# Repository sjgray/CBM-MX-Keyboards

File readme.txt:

CBM MX Keyboards Project         Steve J. Gray
========================

This is a project to create replacement keyboards for CBM Machines
using standard MX keyswitches. The first goal is to create direct
replacements that fit standard CBM cases (if possible).

KEYBOARDS
=========

Keyboards are identified by a string in the following format:

KB-Vn-Rn

where: KB is the keyboard name
       Vn is the version#. This is a unique design/layout of a specific keyboard.
       Rn is the revision#. Generally updates to a specific keyboard version.

 So, take the PET "B" keyboard. V1-R1 is the first design using pcb cutouts to allow the
keyboard to be mounted higher. When this was awkward a R2 revision was done to eliminate
the cutouts and reduce the pcb size. However this requires a 3D printed bracket to mount
it. Since both keyboards use the same switch and keycap layout both are V1. If a new
version is designed that say uses a different sized spacebar or has significant changes
then a V2 would be made. With the CLCD keyboard there are two versions. V1 has a layout
using the diamond arrow cursor keys. A V2 version instead uses an inverted-T cursor layout.

Examples:

       "B-V1-R1" is the PET/CBM "B" (Business) keyboard, Version 1, Revision 1
       "N-V1-R2" is the PET/CBM "N" (Normal/Graphic) keyboard, Version1 , Revision 2

Keyboards In Development:

	N    = PET/CBM Normal/Graphic Keyboard (4032)
	B    = PET/CBM Business Keyboard (8032, SuperPET, 8296 etc)
	CBM2 = B128, CBM128-80, 5x0, 6x0, 7x0,P500 etc
	V364 = TED series prototype with numeric pad
	CLCD = Laptop prototype
	CSX  = C128+SX64 customizable design

Planned:
	C64  = VIC-20, C64, C16 etc
	C65  = C65 with cursor keys etc
	B64  = PET "B" with C64-style layout

STICKERS
========

 Artwork for labelling keycaps is in the STICKERS folder, since that is the most likely
way to label the keys. However, stickers is not the only possibility... see webpage for
more details.

SCANS
=====

  Original keycap scans are in the SCANS folder. These are scanned with a flatbed scanner,
either the entire keyboard (stitched if required) or individual keycap top and front.

WEBPAGE
=======

For more information please visit the project webpage.
Comments and feedback are welcome!

http://www.cbmsteve.ca/mxkeyboards/index.html

HISTORY
=======

KEYBOARD    DATE        PCB?	STATUS
--------    ----        ----	------
B-V1-R1     2020-07-01  YES	Built and tested. Electrically working but requires pcb mounting hole modifications
N-V1-R1     2020-12-17  YES	Built and tested. Electrically working but does not fit in N keyboard case due to measurement error.
N/B         2021-02-10  -	Add keyboard labelling stickers for both N and B keyboards on one page.
N-V1-R2     2021-03-31  -	Add Gerbers
B-V1-R2     2023-03-21	YES	Released. Built and tested.
CSX-V1-R1   2023-09-01  YES	Testing...
CSX-V1-R1   2024-02-25  YES     Released. Built 3 configurations. Basic functionality is working but more work is needed to fully test.
V364        2024-02-25  YES     Released. Built and tested.

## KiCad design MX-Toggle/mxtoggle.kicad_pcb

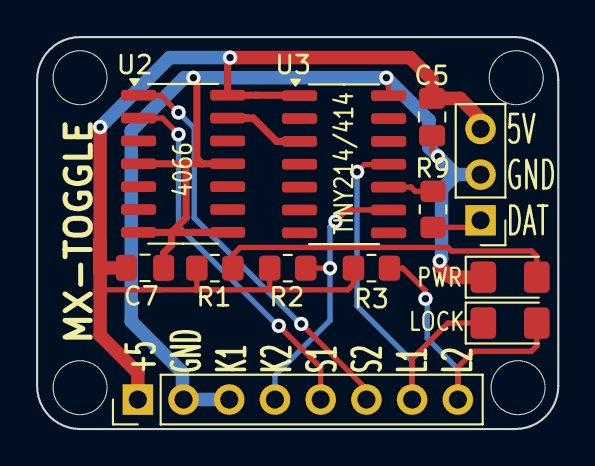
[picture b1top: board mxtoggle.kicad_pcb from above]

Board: 2 copper layers, 29.0 x 21.8 mm, 12 parts (0 on the bottom side), 11 nets.

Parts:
C5, C7: 0.1uf; C_0805_2012Metric_Pad1.18x1.45mm_HandSolder
D1: POWER; D_1206_3216Metric_Pad1.42x1.75mm_HandSolder
D3: SL-LED; D_1206_3216Metric_Pad1.42x1.75mm_HandSolder
J1: HEADER; PinHeader_1x08_P2.54mm_Vertical
J7: UPDI; PinHeader_1x03_P2.54mm_Vertical
R1: 330; R_0805_2012Metric_Pad1.20x1.40mm_HandSolder
R2, R3: R; R_0805_2012Metric_Pad1.20x1.40mm_HandSolder
R9: 470 ohm; R_0805_2012Metric_Pad1.20x1.40mm_HandSolder
U2: CD4066BM; SO-14_3.9x8.65mm_P1.27mm
U3: ATtiny214-SS; SOIC-14_3.9x8.7mm_P1.27mm

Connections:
5V: C5.1, C7.1, J1.1, J7.3, R1.1, R2.1, R3.1, U2.14 (V_{DD}), U3.1 (VCC)
GND: C5.2, C7.2, D1.1 (K), J1.2, J1.3, J7.2, U2.4, U2.7 (V_{SS}), U2.8, U2.11, U3.14 (GND)
KEY: J1.4, R2.2, U3.9 (PB0)
LED1: D3.1 (K), J1.7, U3.11 (PA1)
LED2: D3.2 (A), J1.8, R3.2
unnamed: D1.2 (A), R1.2
unnamed: J7.1, R9.2
SLOUT: U2.13, U3.3 (PA5)
STATE1: J1.5, U2.2
STATE2: J1.6, U2.1
UPDI: R9.1, U3.10 (~RESET/PA0)

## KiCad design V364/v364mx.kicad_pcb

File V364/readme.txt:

V364 MX Keyboard
================

This is a keyboard for the never-released V364 computer which was part of the TED series.
I designed this keyboard based on pictures of prototype machines as part of my project
to recreate the computer. The project is still in development.

I am releasing the design for people that might want a V364 keyboard for their PLUS/4 or
C16 computer which could be placed in a 3D-printed case.

The keyboard is tested and works. The numeric pad does not require any special software
to work as the keys are wired up as duplicates of existing keys in the regular PLUS/4
keyboard.

Steve

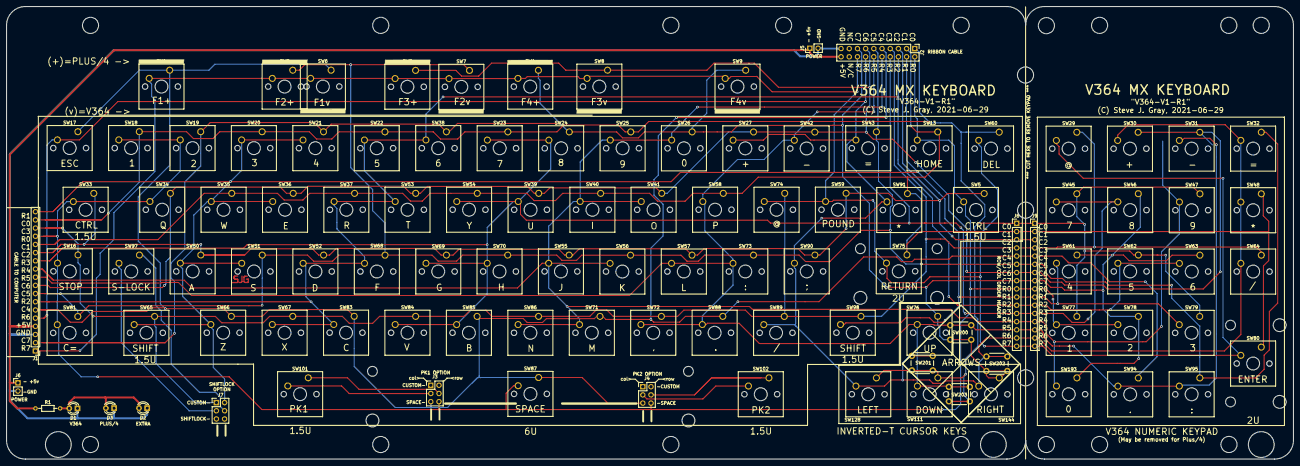
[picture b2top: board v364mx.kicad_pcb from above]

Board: 2 copper layers, 399.1 x 140.3 mm, 109 parts (0 on the bottom side), 25 nets.

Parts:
D1, D2, D3: LED; LED_D3.0mm
J1: MAIN; PinHeader_1x18_P2.54mm_Vertical
J2: RIBBON CONNECTOR; PinHeader_2x10_P2.54mm_Vertical
J3: PK1; PinHeader_2x03_P2.54mm_Vertical
J4: PK2; PinHeader_2x03_P2.54mm_Vertical
J5, J6: POWER; PinHeader_1x02_P2.54mm_Vertical
J7: S-LOCK OPT; PinHeader_2x03_P2.54mm_Vertical
J8: KEYPAD1; PinHeader_1x16_P2.54mm_Vertical
J9: KEYPAD2; PinHeader_1x16_P2.54mm_Vertical
R1: 510; R_Axial_DIN0204_L3.6mm_D1.6mm_P7.62mm_Horizontal
SW1: "F1+"; SW_Cherry_MX_1.00u_PCB
SW2: "F2+"; SW_Cherry_MX_1.00u_PCB
SW3: "F3+"; SW_Cherry_MX_1.00u_PCB
SW4: "F4+"; SW_Cherry_MX_1.00u_PCB
SW5: "CTRL" #2; SW_Cherry_MX_1.50u_PCB
SW6: "F1v"; SW_Cherry_MX_1.00u_PCB
SW7: "F2v"; SW_Cherry_MX_1.00u_PCB
SW8: "F3v"; SW_Cherry_MX_1.00u_PCB
SW9: "F4v"; SW_Cherry_MX_1.00u_PCB
SW13: "HOME"; SW_Cherry_MX_1.00u_PCB
SW16: "STOP"; SW_Cherry_MX_1.00u_PCB
SW17: "ESC"; SW_Cherry_MX_1.00u_PCB
SW18: "1"; SW_Cherry_MX_1.00u_PCB
SW19: "2"; SW_Cherry_MX_1.00u_PCB
SW20: "3"; SW_Cherry_MX_1.00u_PCB
SW21: "4"; SW_Cherry_MX_1.00u_PCB
SW22: "5"; SW_Cherry_MX_1.00u_PCB
SW23: "7"; SW_Cherry_MX_1.00u_PCB
SW24: "8"; SW_Cherry_MX_1.00u_PCB
SW25: "9"; SW_Cherry_MX_1.00u_PCB
SW26: "0"; SW_Cherry_MX_1.00u_PCB
SW27: "+"; SW_Cherry_MX_1.00u_PCB
SW29: KP "@"; SW_Cherry_MX_1.00u_PCB
SW30: KP "+"; SW_Cherry_MX_1.00u_PCB
SW31: KP "-" was KP "*"; SW_Cherry_MX_1.00u_PCB
SW32: KP "="; SW_Cherry_MX_1.00u_PCB
SW33: "CTRL"; SW_Cherry_MX_1.50u_PCB
SW34: "Q"; SW_Cherry_MX_1.00u_PCB
SW35: "W"; SW_Cherry_MX_1.00u_PCB
SW36: "E"; SW_Cherry_MX_1.00u_PCB
SW37: "R"; SW_Cherry_MX_1.00u_PCB
SW38: "6"; SW_Cherry_MX_1.00u_PCB
SW39: "U"; SW_Cherry_MX_1.00u_PCB
SW40: "I"; SW_Cherry_MX_1.00u_PCB
SW41: "O"; SW_Cherry_MX_1.00u_PCB
SW42: "-"; SW_Cherry_MX_1.00u_PCB
SW43: "="; SW_Cherry_MX_1.00u_PCB
SW45: KP "7"; SW_Cherry_MX_1.00u_PCB
SW46: KP "8"; SW_Cherry_MX_1.00u_PCB
SW47: KP "9"; SW_Cherry_MX_1.00u_PCB
SW48: KP "*"; SW_Cherry_MX_1.00u_PCB
SW50: "A"; SW_Cherry_MX_1.00u_PCB
SW51: "S"; SW_Cherry_MX_1.00u_PCB
SW52: "D"; SW_Cherry_MX_1.00u_PCB
SW53: "T"; SW_Cherry_MX_1.00u_PCB
SW54: "Y"; SW_Cherry_MX_1.00u_PCB
SW55: "J"; SW_Cherry_MX_1.00u_PCB
SW56: "K"; SW_Cherry_MX_1.00u_PCB
SW57: "L"; SW_Cherry_MX_1.00u_PCB
SW58: "P"; SW_Cherry_MX_1.00u_PCB
SW59: POUND; SW_Cherry_MX_1.00u_PCB
SW60: "DEL"; SW_Cherry_MX_1.00u_PCB
SW61: KP "4"; SW_Cherry_MX_1.00u_PCB
SW62: KP "5"; SW_Cherry_MX_1.00u_PCB
SW63: KP "6"; SW_Cherry_MX_1.00u_PCB
SW64: KP "/"; SW_Cherry_MX_1.00u_PCB
SW65: "SHIFT"; SW_Cherry_MX_1.50u_PCB
SW66: "Z"; SW_Cherry_MX_1.00u_PCB
SW67: "X"; SW_Cherry_MX_1.00u_PCB
SW68: "F"; SW_Cherry_MX_1.00u_PCB
SW69: "G"; SW_Cherry_MX_1.00u_PCB
SW70: "H"; SW_Cherry_MX_1.00u_PCB
SW71: "M"; SW_Cherry_MX_1.00u_PCB
SW72: ","; SW_Cherry_MX_1.00u_PCB
SW73: ":"; SW_Cherry_MX_1.00u_PCB
SW74: "@"; SW_Cherry_MX_1.00u_PCB
SW75: "RETURN"; SW_Cherry_MX_2.00u_PCB
SW76: "UP"; SW_Cherry_MX_1.00u_PCB
SW77: KP "1"; SW_Cherry_MX_1.00u_PCB
SW78: KP "2"; SW_Cherry_MX_1.00u_PCB
SW79: KP "3"; SW_Cherry_MX_1.00u_PCB
SW80: "ENTER"; SW_Cherry_MX_2.00u_Vertical_PCB
SW81: "C="; SW_Cherry_MX_1.00u_PCB
SW83: "C"; SW_Cherry_MX_1.00u_PCB
SW84: "V"; SW_Cherry_MX_1.00u_PCB
SW85: "B"; SW_Cherry_MX_1.00u_PCB
SW86: "N"; SW_Cherry_MX_1.00u_PCB
SW87: "SPACE"; SW_Cherry_MX_6.0u_PCB
SW88: "."; SW_Cherry_MX_1.00u_PCB
SW89: "/"; SW_Cherry_MX_1.00u_PCB
SW90: ";]" was "'"; SW_Cherry_MX_1.00u_PCB
SW91: "*" was "PI"; SW_Cherry_MX_1.00u_PCB
SW94: KP "."; SW_Cherry_MX_1.00u_PCB
SW95: KP ":" was KP "00"; SW_Cherry_MX_1.00u_PCB
SW97: S-LOCK; SW_Cherry_MX_1.00u_PCB
SW98: R-SHIFT; SW_Cherry_MX_1.50u_PCB
SW101: PRG1; SW_Cherry_MX_1.50u_PCB
SW102: PRG2; SW_Cherry_MX_1.50u_PCB
SW111: "DOWN"; SW_Cherry_MX_1.00u_PCB
SW128: "LEFT"; SW_Cherry_MX_1.00u_PCB
SW144: "RIGHT"; SW_Cherry_MX_1.00u_PCB
SW193: KP"0"; SW_Cherry_MX_1.00u_PCB
SW200: UP; SW_PUSH_6mm
SW201: LEFT; SW_PUSH_6mm
SW202: RIGHT; SW_PUSH_6mm
SW203: DOWN; SW_PUSH_6mm

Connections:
5V: J1.4, J2.20, J5.1, J6.1, R1.1
C0: J1.17, J2.1, J8.1, J9.1, SW18.1, SW20.1, SW22.1, SW23.1, SW25.1, SW45.1, SW47.1, SW60.1, SW62.1, SW77.1, SW79.1, SW111.1, SW128.1, SW201.2, SW203.2
C1: J1.14, J2.3, J8.2, J9.2, SW13.1, SW35.1, SW37.1, SW40.1, SW48.1, SW54.1, SW58.1, SW75.1, SW80.1, SW91.1
C2: J1.13, J2.5, J8.3, J9.3, SW5.1, SW33.1, SW50.1, SW52.1, SW55.1, SW57.1, SW59.1, SW69.1, SW90.1
C3: J1.16, J2.7, J7.1, J8.4, J9.4, SW16.1, SW29.1, SW64.1, SW65.1, SW67.1, SW72.1, SW74.1, SW84.1, SW86.1, SW89.1, SW98.1
C4: J1.6, J2.9, J3.5, J4.5, J8.5, J9.5, SW1.1, SW6.1, SW17.1, SW66.1, SW71.1, SW83.1, SW85.1, SW87.1, SW88.1, SW94.1
C5: J1.8, J2.11, J8.6, J9.6, SW2.1, SW7.1, SW32.1, SW43.1, SW51.1, SW56.1, SW68.1, SW70.1, SW73.1, SW81.1, SW95.1
C6: J1.9, J2.13, J8.7, J9.7, SW3.1, SW8.1, SW27.1, SW30.1, SW31.1, SW34.1, SW36.1, SW39.1, SW41.1, SW42.1, SW53.1
C7: J1.2, J2.15, J8.8, J9.8, SW4.1, SW9.1, SW19.1, SW21.1, SW24.1, SW26.1, SW38.1, SW46.1, SW61.1, SW63.1, SW76.1, SW78.1, SW144.1, SW193.1, SW200.2, SW202.2
GND: D1.1, D2.1, D3.1, J1.3, J2.19, J5.2, J6.2
unnamed: D1.2, D2.2, D3.2, R1.2
PK1C: J3.3, SW101.2
PK1R: J3.4, SW101.1
PK2C: J4.3, SW102.2
PK2R: J4.4, SW102.1
R0: J1.15, J2.2, J3.6, J4.6, J8.9, J9.9, SW5.2, SW13.2, SW16.2, SW18.2, SW19.2, SW33.2, SW34.2, SW77.2, SW78.2, SW81.2, SW87.2
R1: J1.18, J2.4, J7.2, J8.10, J9.10, SW20.2, SW21.2, SW35.2, SW36.2, SW50.2, SW51.2, SW61.2, SW65.2, SW66.2, SW79.2, SW98.2
R2: J1.7, J2.6, J8.11, J9.11, SW22.2, SW37.2, SW38.2, SW52.2, SW53.2, SW62.2, SW63.2, SW67.2, SW68.2, SW83.2
R3: J1.12, J2.8, J8.12, J9.12, SW23.2, SW24.2, SW39.2, SW45.2, SW46.2, SW54.2, SW69.2, SW70.2, SW84.2, SW85.2
R4: J1.11, J2.10, J8.13, J9.13, SW25.2, SW26.2, SW40.2, SW41.2, SW47.2, SW55.2, SW56.2, SW71.2, SW86.2, SW193.2
R5: J1.10, J2.12, J8.14, J9.14, SW31.2, SW42.2, SW57.2, SW58.2, SW72.2, SW73.2, SW76.2, SW88.2, SW94.2, SW95.2, SW111.2, SW200.1, SW203.1
R6: J1.5, J2.14, J8.15, J9.15, SW17.2, SW27.2, SW30.2, SW32.2, SW43.2, SW48.2, SW64.2, SW89.2, SW90.2, SW91.2, SW128.2, SW144.2, SW201.1, SW202.1
R7: J1.1, J2.16, J8.16, J9.16, SW1.2, SW2.2, SW3.2, SW4.2, SW6.2, SW7.2, SW8.2, SW9.2, SW29.2, SW59.2, SW60.2, SW74.2, SW75.2, SW80.2
SLOCKC: J7.3, SW97.2
SLOCKR: J7.4, SW97.1

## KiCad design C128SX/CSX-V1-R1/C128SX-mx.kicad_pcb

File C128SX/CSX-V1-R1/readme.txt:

C128SX MX Keyboard
================== 

V1R1 Completed 2023-09-01

*** This keyboard is still in development! ***

 This is an MX keyboard with multiple possible configurations by snapping
off sections or populating keys in different locations and setting jumpers.
This design can use standard MX keyswitches, or Gateron Low-Profile
switches. I recommend Low-Profile when making C128 or SX64 keyboards.

There are 4 sections:

 1) Main section - Letters, numbers, spacebar, cursor etc.
 2) The C128 top row keys: ESC, Scroll lock, 40/80, cursor, function keys.
 3) Numeric pad.
 4) SX64 function keys (embedded in numeric pad).

The Main section has an option for an inverted-T cursor that can be enabled
by populating U1 and setting jumpers. This is handled like the C65 keyboard
where the UP and RIGHT keys are simulated by virtually pressing the SHIFT
key, and are transparent to the computer.

The C128 top row has an option to relocate the function keys to replace the
redundant cursor keys. It also has an option to use a special set of
function keys in a Plus/4 function keys style for use in C64 mode.

The NUMERIC PAD is not wired like the C128 expects, but is instead wired
into the main layout. This allows them to be used in C64 mode without any
special software. The drawback is that these keys can no longer be detected
separately from the normal number keys in C128 mode.

The SX Function Keys occupy the same space as the left side of the numeric
keypad. The MX switches must be installed in the correct locations and in
the correct orientation.

----

I have built the following configurations:
	- SX64 standard layout.
 	- C128 standard layout.
        - C64 with Plus/4-style function keys on top.

The configurations above are partially working:
	- General layout and matrix are ok.
	- Snap-off sections are ok.
	- Numeric pad works on C128 and C64.

- Not Tested:
	- Locking keys.
	- Inverted-T.
	- SX64 DB25 alignment.
	- Mounting hole alignment.

- The first revision is made available for those that need a BASIC
  replacement keyboard and do not need shift-lock or other locking
  keys.

- You can send the GERBERS to JLCPCB but they will need so adjustment
  and extra charges for the additional slots (about $7 extra per 5 boards).

- Fixes for next release:
	- Fix SX64 alignment hole position (move right)
	- Fix SX64 and C128 mounting holes
	- Reduce holes in between breakaway traces from 2.0mm to 1.8mm.
	- Move top breakaway slots down for better fit with SX config
	- Add jumpers for standard SX-64 SHIFT-LOCK (bypass ATTINY circuit)
	- Investigate adding upside-down switches for TED (V364, C16) mode:
		- R-SHIFT connect as L-SHIFT
		- BACKARROW to ESC
		- UP/DOWN key seems to have no function
		- Check other badly located keys

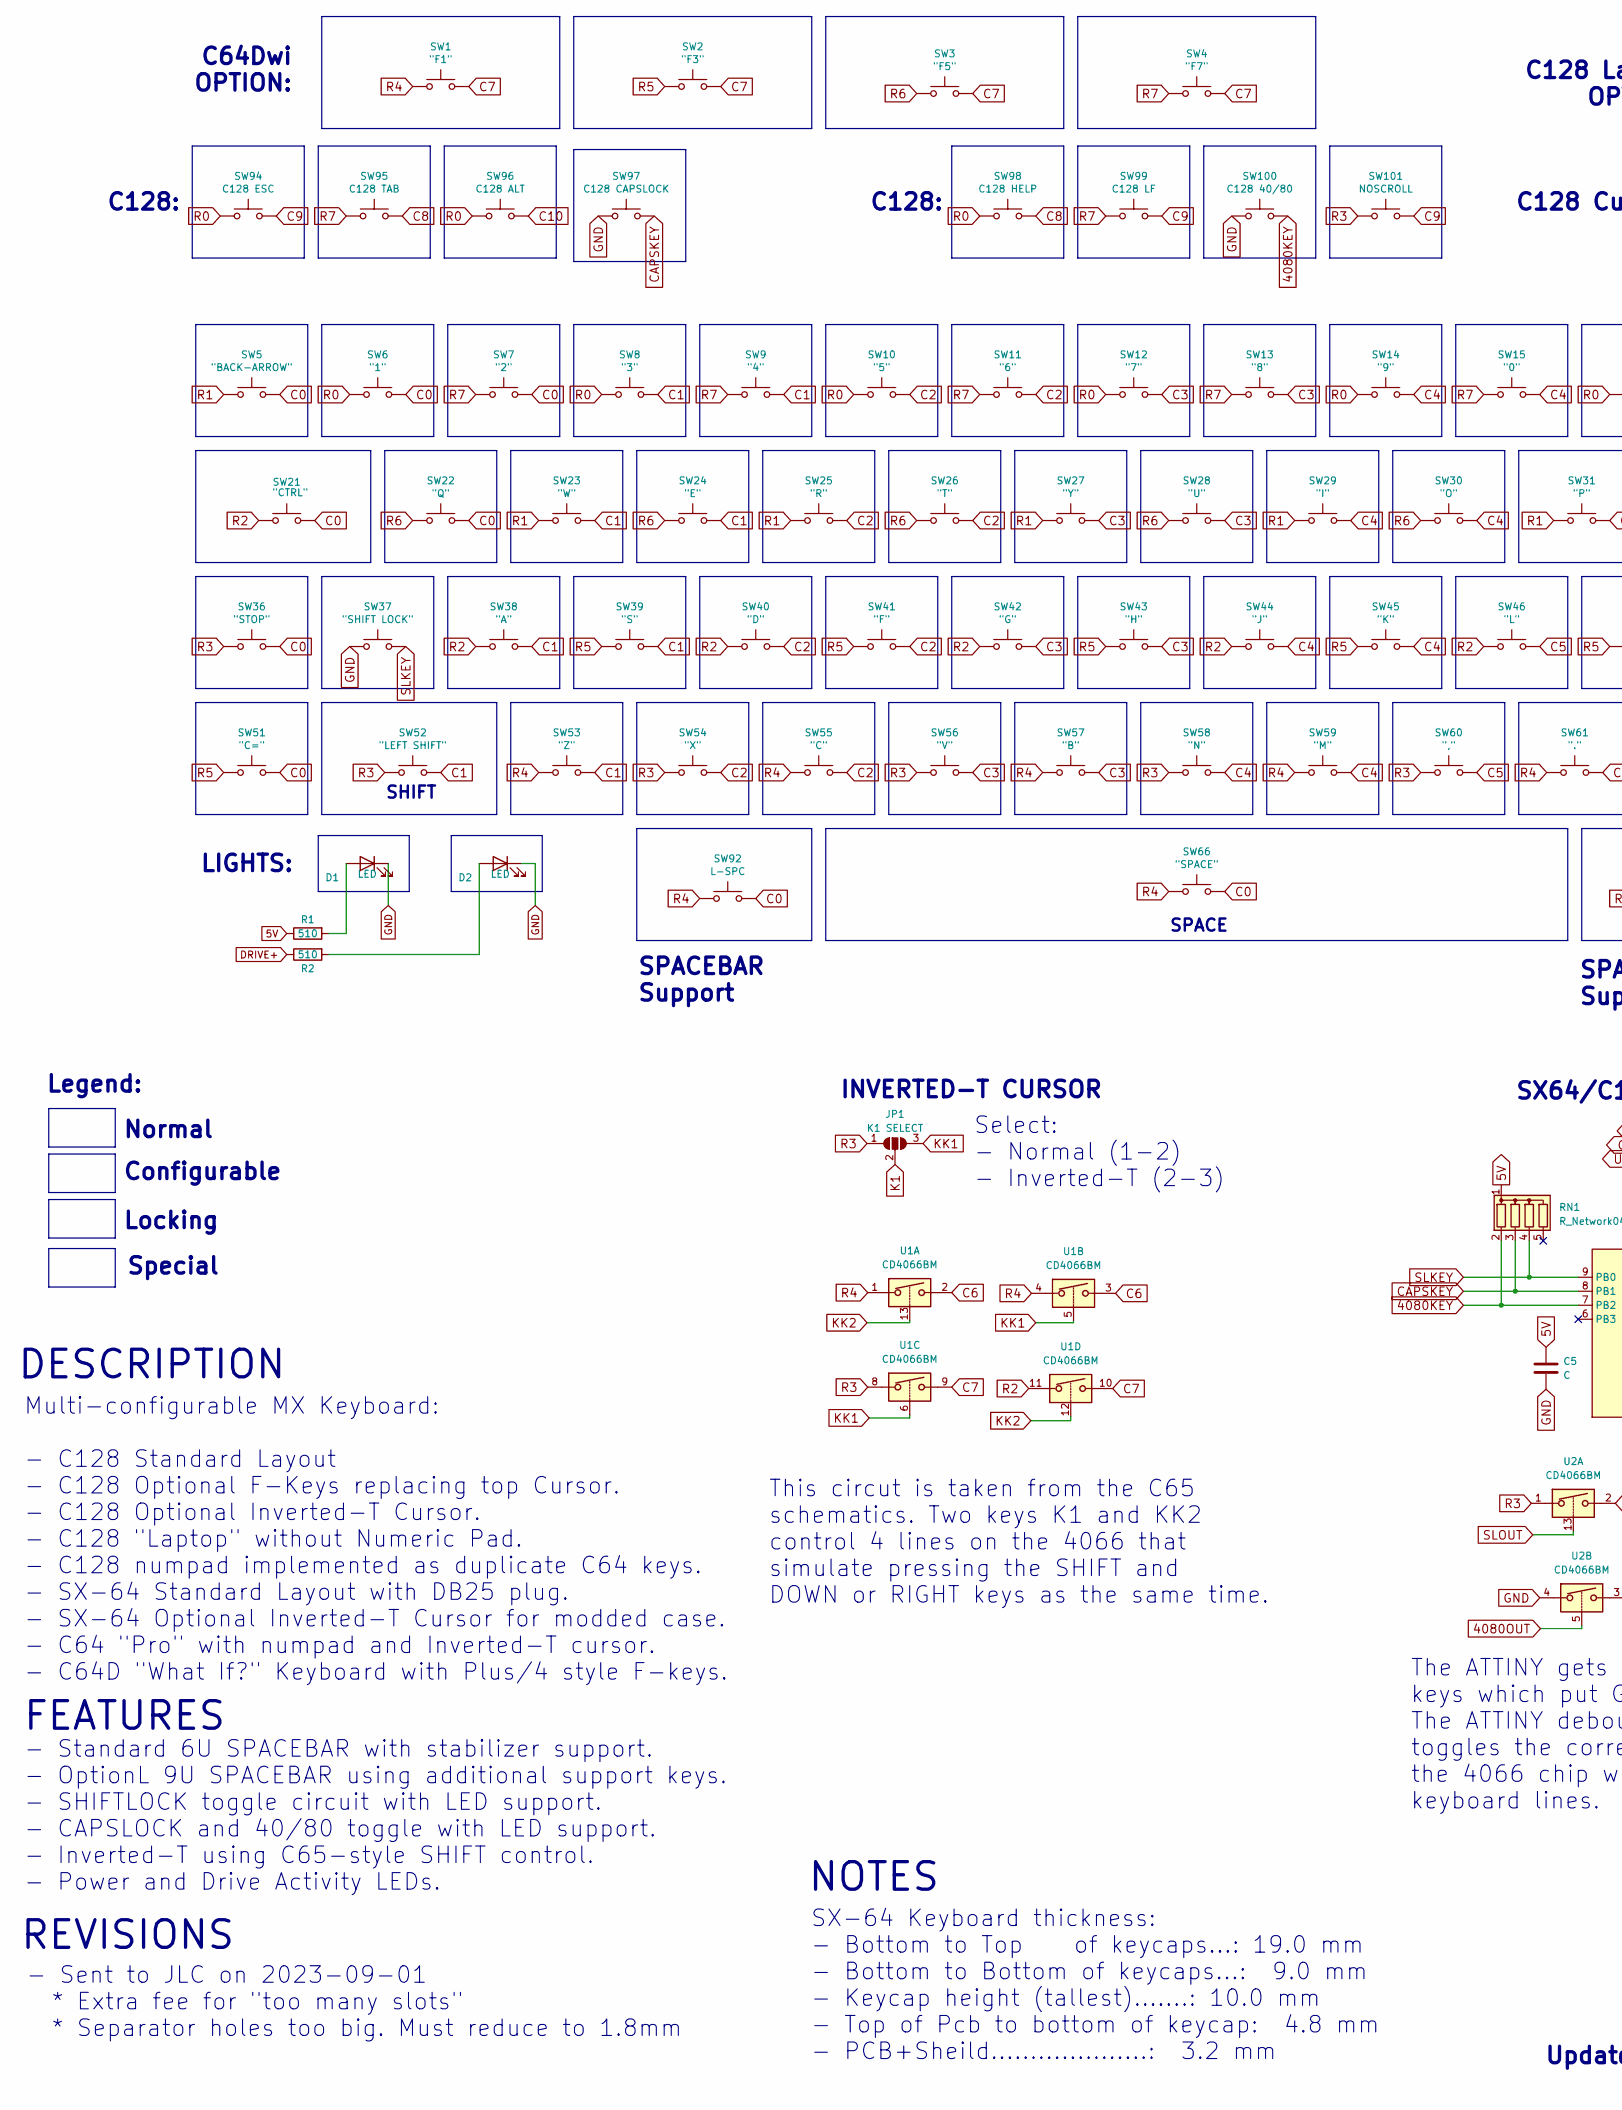
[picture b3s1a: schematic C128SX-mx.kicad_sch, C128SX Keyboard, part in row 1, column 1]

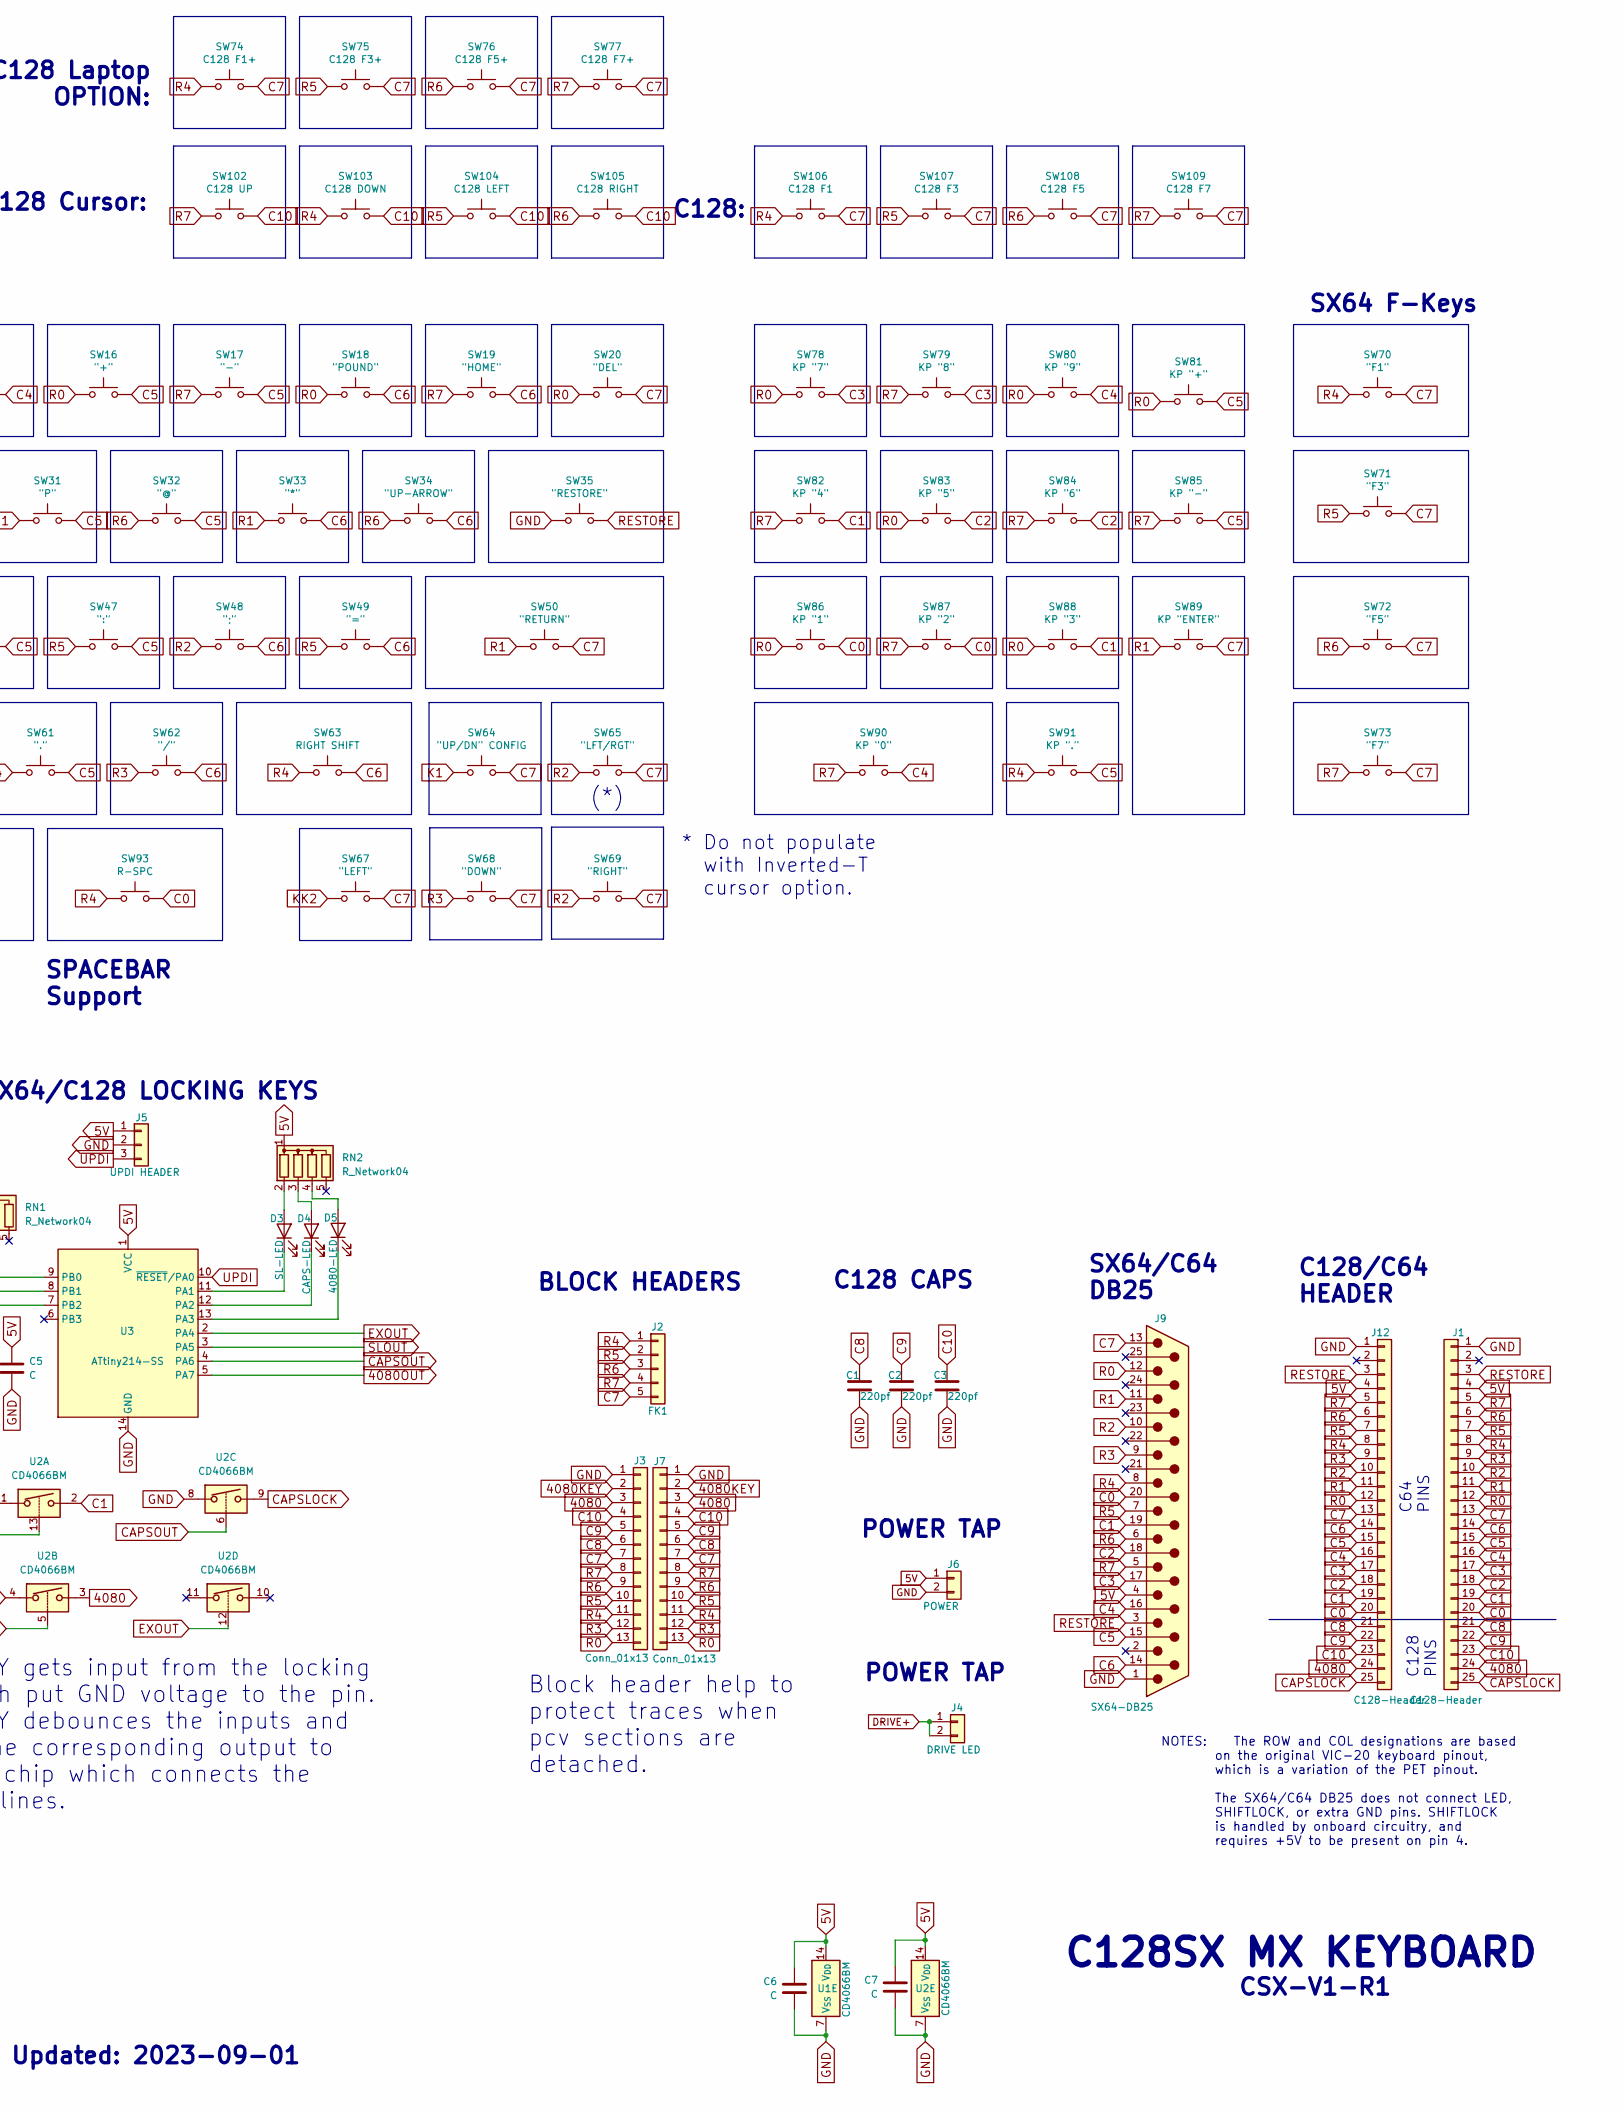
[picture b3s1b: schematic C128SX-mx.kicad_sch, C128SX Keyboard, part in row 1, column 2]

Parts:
C1, C2, C3: 220pf; C_Disc_D4.7mm_W2.5mm_P5.00mm
C5, C6, C7: C; C_Disc_D5.0mm_W2.5mm_P5.00mm
D1, D2: LED; LED_D3.0mm
D3: SL-LED; LED_D3.0mm
D4: CAPS-LED; LED_D3.0mm
D5: 4080-LED; LED_D3.0mm
J1, J12: C128-Header; PinHeader_1x25_P2.54mm_Vertical
J2: FK1; PinHeader_1x05_P2.54mm_Vertical
J3, J7: Conn_01x13; PinHeader_1x13_P2.54mm_Vertical
J4: DRIVE LED; PinHeader_1x02_P2.54mm_Vertical
J5: UPDI HEADER; PinHeader_1x03_P2.54mm_Vertical
J6: POWER; PinHeader_1x02_P2.54mm_Vertical
J9: SX64-DB25; DSUB-25_Female_Horizontal_P2.77x2.84mm_EdgePinOffset7.70mm_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
JP1: K1 SELECT; SolderJumper-3_P1.3mm_Open_RoundedPad1.0x1.5mm_NumberLabels
R1, R2: 510; R_Axial_DIN0204_L3.6mm_D1.6mm_P7.62mm_Horizontal
RN1, RN2: R_Network04; R_Array_SIP5
SW1, SW70: "F1"; SW_Hybrid_CherryMX_GateronLP_1.00u_PCB
SW2, SW71: "F3"; SW_Hybrid_CherryMX_GateronLP_1.00u_PCB
SW3, SW72: "F5"; SW_Hybrid_CherryMX_GateronLP_1.00u_PCB
SW4, SW73: "F7"; SW_Hybrid_CherryMX_GateronLP_1.00u_PCB
SW5: "BACK-ARROW"; SW_Hybrid_CherryMX_GateronLP_1.00u_PCB
SW6: "1"; SW_Hybrid_CherryMX_GateronLP_1.00u_PCB
SW7: "2"; SW_Hybrid_CherryMX_GateronLP_1.00u_PCB
SW8: "3"; SW_Hybrid_CherryMX_GateronLP_1.00u_PCB
SW9: "4"; SW_Hybrid_CherryMX_GateronLP_1.00u_PCB
SW10: "5"; SW_Hybrid_CherryMX_GateronLP_1.00u_PCB
SW11: "6"; SW_Hybrid_CherryMX_GateronLP_1.00u_PCB
SW12: "7"; SW_Hybrid_CherryMX_GateronLP_1.00u_PCB
SW13: "8"; SW_Hybrid_CherryMX_GateronLP_1.00u_PCB
SW14: "9"; SW_Hybrid_CherryMX_GateronLP_1.00u_PCB
SW15: "0"; SW_Hybrid_CherryMX_GateronLP_1.00u_PCB
SW16: "+"; SW_Hybrid_CherryMX_GateronLP_1.00u_PCB
SW17: "-"; SW_Hybrid_CherryMX_GateronLP_1.00u_PCB
SW18: "POUND"; SW_Hybrid_CherryMX_GateronLP_1.00u_PCB
SW19: "HOME"; SW_Hybrid_CherryMX_GateronLP_1.00u_PCB
SW20: "DEL"; SW_Hybrid_CherryMX_GateronLP_1.00u_PCB
SW21: "CTRL"; SW_Hybrid_CherryMX_GateronLP_1.50u_PCB
SW22: "Q"; SW_Hybrid_CherryMX_GateronLP_1.00u_PCB
SW23: "W"; SW_Hybrid_CherryMX_GateronLP_1.00u_PCB
SW24: "E"; SW_Hybrid_CherryMX_GateronLP_1.00u_PCB
SW25: "R"; SW_Hybrid_CherryMX_GateronLP_1.00u_PCB
SW26: "T"; SW_Hybrid_CherryMX_GateronLP_1.00u_PCB
SW27: "Y"; SW_Hybrid_CherryMX_GateronLP_1.00u_PCB
SW28: "U"; SW_Hybrid_CherryMX_GateronLP_1.00u_PCB
SW29: "I"; SW_Hybrid_CherryMX_GateronLP_1.00u_PCB
SW30: "O"; SW_Hybrid_CherryMX_GateronLP_1.00u_PCB
SW31: "P"; SW_Hybrid_CherryMX_GateronLP_1.00u_PCB
SW32: "@"; SW_Hybrid_CherryMX_GateronLP_1.00u_PCB
SW33: "*"; SW_Hybrid_CherryMX_GateronLP_1.00u_PCB
SW34: "UP-ARROW"; SW_Hybrid_CherryMX_GateronLP_1.00u_PCB
SW35: "RESTORE"; SW_Hybrid_CherryMX_GateronLP_1.50u_PCB
SW36: "STOP"; SW_Hybrid_CherryMX_GateronLP_1.00u_PCB
SW37: "SHIFT LOCK"; SW_Hybrid_CherryMX_GateronLP_1.00u_PCB
SW38: "A"; SW_Hybrid_CherryMX_GateronLP_1.00u_PCB
SW39: "S"; SW_Hybrid_CherryMX_GateronLP_1.00u_PCB
SW40: "D"; SW_Hybrid_CherryMX_GateronLP_1.00u_PCB
SW41: "F"; SW_Hybrid_CherryMX_GateronLP_1.00u_PCB
SW42: "G"; SW_Hybrid_CherryMX_GateronLP_1.00u_PCB
SW43: "H"; SW_Hybrid_CherryMX_GateronLP_1.00u_PCB
SW44: "J"; SW_Hybrid_CherryMX_GateronLP_1.00u_PCB
SW45: "K"; SW_Hybrid_CherryMX_GateronLP_1.00u_PCB
SW46: "L"; SW_Hybrid_CherryMX_GateronLP_1.00u_PCB
SW47: ":"; SW_Hybrid_CherryMX_GateronLP_1.00u_PCB
SW48: ";"; SW_Hybrid_CherryMX_GateronLP_1.00u_PCB
SW49: "="; SW_Hybrid_CherryMX_GateronLP_1.00u_PCB
SW50: "RETURN"; SW_Hybrid_CherryMX_GateronLP_2.00u_PCB
SW51: "C="; SW_Hybrid_CherryMX_GateronLP_1.00u_PCB
SW52: "LEFT SHIFT"; SW_Hybrid_CherryMX_GateronLP_1.50u_PCB
SW53: "Z"; SW_Hybrid_CherryMX_GateronLP_1.00u_PCB
SW54: "X"; SW_Hybrid_CherryMX_GateronLP_1.00u_PCB
SW55: "C"; SW_Hybrid_CherryMX_GateronLP_1.00u_PCB
SW56: "V"; SW_Hybrid_CherryMX_GateronLP_1.00u_PCB
SW57: "B"; SW_Hybrid_CherryMX_GateronLP_1.00u_PCB
SW58: "N"; SW_Hybrid_CherryMX_GateronLP_1.00u_PCB
SW59: "M"; SW_Hybrid_CherryMX_GateronLP_1.00u_PCB
SW60: ","; SW_Hybrid_CherryMX_GateronLP_1.00u_PCB
SW61: "."; SW_Hybrid_CherryMX_GateronLP_1.00u_PCB
SW62: "/"; SW_Hybrid_CherryMX_GateronLP_1.00u_PCB
SW63: RIGHT SHIFT; SW_Hybrid_CherryMX_GateronLP_1.50u_PCB
SW64: "UP/DN" CONFIG; SW_Hybrid_CherryMX_GateronLP_1.00u_PCB
SW65: "LFT/RGT"; SW_Hybrid_CherryMX_GateronLP_1.00u_PCB
SW66: "SPACE"; SW_Hybrid_CherryMX_GateronLP_6.0u_Stabs_PCB
SW67: "LEFT"; SW_Hybrid_CherryMX_GateronLP_1.00u_PCB
SW68: "DOWN"; SW_Hybrid_CherryMX_GateronLP_1.00u_PCB
SW69: "RIGHT"; SW_Hybrid_CherryMX_GateronLP_1.00u_PCB
SW74: C128 F1+; SW_Hybrid_CherryMX_GateronLP_1.00u_PCB
SW75: C128 F3+; SW_Hybrid_CherryMX_GateronLP_1.00u_PCB
SW76: C128 F5+; SW_Hybrid_CherryMX_GateronLP_1.00u_PCB
SW77: C128 F7+; SW_Hybrid_CherryMX_GateronLP_1.00u_PCB
SW78: KP "7"; SW_Hybrid_CherryMX_GateronLP_1.00u_PCB
SW79: KP "8"; SW_Hybrid_CherryMX_GateronLP_1.00u_PCB
SW80: KP "9"; SW_Hybrid_CherryMX_GateronLP_1.00u_PCB
SW81: KP "+"; SW_Hybrid_CherryMX_GateronLP_1.00u_PCB
SW82: KP "4"; SW_Hybrid_CherryMX_GateronLP_1.00u_PCB
SW83: KP "5"; SW_Hybrid_CherryMX_GateronLP_1.00u_PCB
SW84: KP "6"; SW_Hybrid_CherryMX_GateronLP_1.00u_PCB
SW85: KP "-"; SW_Hybrid_CherryMX_GateronLP_1.00u_PCB
SW86: KP "1"; SW_Hybrid_CherryMX_GateronLP_1.00u_PCB
SW87: KP "2"; SW_Hybrid_CherryMX_GateronLP_1.00u_PCB
SW88: KP "3"; SW_Hybrid_CherryMX_GateronLP_1.00u_PCB
SW89: KP "ENTER"; SW_Hybrid_CherryMX_GateronLP_2.00u_Vertical_PCB
SW90: KP "0"; SW_Hybrid_CherryMX_GateronLP_2.00u_NoStab_PCB
SW91: KP "."; SW_Hybrid_CherryMX_GateronLP_1.00u_PCB
SW92: L-SPC; SW_Hybrid_CherryMX_GateronLP_1.50u_PCB
SW93: R-SPC; SW_Hybrid_CherryMX_GateronLP_1.50u_PCB
SW94: C128 ESC; SW_Hybrid_CherryMX_GateronLP_1.00u_PCB
SW95: C128 TAB; SW_Hybrid_CherryMX_GateronLP_1.00u_PCB
SW96: C128 ALT; SW_Hybrid_CherryMX_GateronLP_1.00u_PCB
SW97: C128 CAPSLOCK; SW_Hybrid_CherryMX_GateronLP_1.00u_PCB
SW98: C128 HELP; SW_Hybrid_CherryMX_GateronLP_1.00u_PCB
SW99: C128 LF; SW_Hybrid_CherryMX_GateronLP_1.00u_PCB
SW100: C128 40/80; SW_Hybrid_CherryMX_GateronLP_1.00u_PCB
SW101: NOSCROLL; SW_Hybrid_CherryMX_GateronLP_1.00u_PCB
SW102: C128 UP; SW_Hybrid_CherryMX_GateronLP_1.00u_PCB
SW103: C128 DOWN; SW_Hybrid_CherryMX_GateronLP_1.00u_PCB
SW104: C128 LEFT; SW_Hybrid_CherryMX_GateronLP_1.00u_PCB
SW105: C128 RIGHT; SW_Hybrid_CherryMX_GateronLP_1.00u_PCB
SW106: C128 F1; SW_Hybrid_CherryMX_GateronLP_1.00u_PCB
SW107: C128 F3; SW_Hybrid_CherryMX_GateronLP_1.00u_PCB
SW108: C128 F5; SW_Hybrid_CherryMX_GateronLP_1.00u_PCB
SW109: C128 F7; SW_Hybrid_CherryMX_GateronLP_1.00u_PCB
U1, U2: CD4066BM; SO-14_3.9x8.65mm_P1.27mm
U3: ATtiny214-SS; SOIC-14_3.9x8.7mm_P1.27mm

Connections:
5V: C5.1, C6.1, C7.1, J1.4, J5.1, J6.1, J9.4, J12.4, R1.1, RN1.1 (common), RN2.1 (common), U1.14 (V_{DD}), U2.14 (V_{DD}), U3.1 (VCC)
4080: J1.24, J3.3, J7.3, J12.24, U2.3
4080KEY: J3.2, J7.2, RN1.2 (R1), SW100.2, U3.7 (PB2)
4080OUT: U2.5, U3.5 (PA7)
C0: J1.20, J9.20, J12.20, SW5.2, SW6.2, SW7.2, SW21.2, SW22.2, SW36.2, SW51.2, SW66.2, SW86.2, SW87.2, SW92.2, SW93.2
C1: J1.19, J9.19, J12.19, SW8.2, SW9.2, SW23.2, SW24.2, SW38.2, SW39.2, SW52.2, SW53.2, SW82.2, SW88.2, U2.2
C2: J1.18, J9.18, J12.18, SW10.2, SW11.2, SW25.2, SW26.2, SW40.2, SW41.2, SW54.2, SW55.2, SW83.2, SW84.2
C3: J1.17, J9.17, J12.17, SW12.2, SW13.2, SW27.2, SW28.2, SW42.2, SW43.2, SW56.2, SW57.2, SW78.2, SW79.2
C4: J1.16, J9.16, J12.16, SW14.2, SW15.2, SW29.2, SW30.2, SW44.2, SW45.2, SW58.2, SW59.2, SW80.2, SW90.2
C5: J1.15, J9.15, J12.15, SW16.2, SW17.2, SW31.2, SW32.2, SW46.2, SW47.2, SW60.2, SW61.2, SW81.2, SW85.2, SW91.2
C6: J1.14, J9.14, J12.14, SW18.2, SW19.2, SW33.2, SW34.2, SW48.2, SW49.2, SW62.2, SW63.2, U1.2, U1.3
C7: J1.13, J2.5, J3.7, J7.7, J9.13, J12.13, SW1.2, SW2.2, SW3.2, SW4.2, SW20.2, SW50.2, SW64.2, SW65.2, SW67.2, SW68.2, SW69.2, SW70.2, SW71.2, SW72.2, SW73.2, SW74.2, SW75.2, SW76.2, SW77.2, SW89.2, SW106.2, SW107.2, SW108.2, SW109.2, U1.9, U1.10
C8: C1.1, J1.21, J3.6, J7.6, J12.21, SW95.2, SW98.2
C9: C2.1, J1.22, J3.5, J7.5, J12.22, SW94.2, SW99.2, SW101.2
C10: C3.1, J1.23, J3.4, J7.4, J12.23, SW96.2, SW102.2, SW103.2, SW104.2, SW105.2
CAPSKEY: RN1.3 (R2), SW97.2, U3.8 (PB1)
CAPSLOCK: J1.25, J12.25, U2.9
CAPSOUT: U2.6, U3.4 (PA6)
DRIVE+: J4.1, J4.2, R2.1
EXOUT: U2.12, U3.2 (PA4)
GND: C1.2, C2.2, C3.2, C5.2, C6.2, C7.2, D1.1 (K), D2.1 (K), J1.1, J3.1, J5.2, J6.2, J7.1, J9.1, J12.1, SW35.1, SW37.1, SW97.1, SW100.1, U1.7 (V_{SS}), U2.4, U2.7 (V_{SS}), U2.8, U3.14 (GND)
K1: JP1.2 (C), SW64.1
KK1: JP1.3 (B), U1.5, U1.6
KK2: SW67.1, U1.12
unnamed: D1.2 (A), R1.2
unnamed: D2.2 (A), R2.2
unnamed: D3.2 (A), RN2.2 (R1)
unnamed: D3.1 (K), U3.11 (PA1)
unnamed: D4.2 (A), RN2.3 (R2)
unnamed: D4.1 (K), U3.12 (PA2)
unnamed: D5.2 (A), RN2.4 (R3)
unnamed: D5.1 (K), U3.13 (PA3)
R0: J1.12, J3.13, J7.13, J9.12, J12.12, SW6.1, SW8.1, SW10.1, SW12.1, SW14.1, SW16.1, SW18.1, SW20.1, SW78.1, SW80.1, SW81.1, SW83.1, SW86.1, SW88.1, SW94.1, SW96.1, SW98.1
R1: J1.11, J9.11, J12.11, SW5.1, SW23.1, SW25.1, SW27.1, SW29.1, SW31.1, SW33.1, SW50.1, SW89.1
R2: J1.10, J9.10, J12.10, SW21.1, SW38.1, SW40.1, SW42.1, SW44.1, SW46.1, SW48.1, SW65.1, SW69.1, U1.11
R3: J1.9, J3.12, J7.12, J9.9, J12.9, JP1.1 (A), SW36.1, SW52.1, SW54.1, SW56.1, SW58.1, SW60.1, SW62.1, SW68.1, SW101.1, U1.8, U2.1
R4: J1.8, J2.1, J3.11, J7.11, J9.8, J12.8, SW1.1, SW53.1, SW55.1, SW57.1, SW59.1, SW61.1, SW63.1, SW66.1, SW70.1, SW74.1, SW91.1, SW92.1, SW93.1, SW103.1, SW106.1, U1.1, U1.4
R5: J1.7, J2.2, J3.10, J7.10, J9.7, J12.7, SW2.1, SW39.1, SW41.1, SW43.1, SW45.1, SW47.1, SW49.1, SW51.1, SW71.1, SW75.1, SW104.1, SW107.1
R6: J1.6, J2.3, J3.9, J7.9, J9.6, J12.6, SW3.1, SW22.1, SW24.1, SW26.1, SW28.1, SW30.1, SW32.1, SW34.1, SW72.1, SW76.1, SW105.1, SW108.1
R7: J1.5, J2.4, J3.8, J7.8, J9.5, J12.5, SW4.1, SW7.1, SW9.1, SW11.1, SW13.1, SW15.1, SW17.1, SW19.1, SW73.1, SW77.1, SW79.1, SW82.1, SW84.1, SW85.1, SW87.1, SW90.1, SW95.1, SW99.1, SW102.1, SW109.1
RESTORE: J1.3, J9.3, J12.3, SW35.2
SLKEY: RN1.4 (R3), SW37.2, U3.9 (PB0)
SLOUT: U3.3 (PA5)
UPDI: J5.3, U3.10 (~RESET/PA0)

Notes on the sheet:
C128 Laptop OPTION:
SHIFT
DESCRIPTION
Legend:
Normal
SPACE
SPACEBAR Support
C64Dwi OPTION:
- Standard 6U SPACEBAR with stabilizer support. - OptionL 9U SPACEBAR using additional support keys. - SHIFTLOCK toggle circuit with LED support. - CAPSLOCK and 40/80 toggle with LED support. - Inverted-T using C65-style SHIFT control. - Power and Drive Activity LEDs.
Select: - Normal (1-2) - Inverted-T (2-3)
SX64/C128 LOCKING KEYS
C128:
BLOCK HEADERS
POWER TAP
(*)
SX-64 Keyboard thickness: - Bottom to Top of keycaps...: 19.0 mm - Bottom to Bottom of keycaps...: 9.0 mm - Keycap height (tallest).......: 10.0 mm - Top of Pcb to bottom of keycap: 4.8 mm - PCB+Sheild....................: 3.2 mm
C128 Cursor:
NOTES
The ATTINY gets input from the locking keys which put GND voltage to the pin. The ATTINY debounces the inputs and toggles the corresponding output to the 4066 chip which connects the keyboard lines.
INVERTED-T CURSOR
LIGHTS:
Locking
Multi-configurable MX Keyboard: - C128 Standard Layout - C128 Optional F-Keys replacing top Cursor. - C128 Optional Inverted-T Cursor. - C128 "Laptop" without Numeric Pad. - C128 numpad implemented as duplicate C64 keys. - SX-64 Standard Layout with DB25 plug. - SX-64 Optional Inverted-T Cursor for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
CSX-V1-R1
SX64 F-Keys
SX64/C64 DB25
C128 CAPS
Configurable
C128/C64 HEADER
Block header help to protect traces when pcv sections are detached.
C128SX MX KEYBOARD
REVISIONS
FEATURES
* Do not populate with Inverted-T cursor option.
This circut is taken from the C65 schematics. Two keys K1 and KK2 control 4 lines on the 4066 that simulate pressing the SHIFT and DOWN or RIGHT keys as the same time.
Updated: 2023-09-01
- Sent to JLC on 2023-09-01 * Extra fee for "too many slots" * Separator holes too big. Must reduce to 1.8mm
C64 PINS
C128 PINS
NOTES: The ROW and COL designations are based on the original VIC-20 keyboard pinout, which is a variation of the PET pinout. The SX64/C64 DB25 does not connect LED, SHIFTLOCK, or extra GND pins. SHIFTLOCK is handled by onboard circuitry, and requires +5V to be present on pin 4.

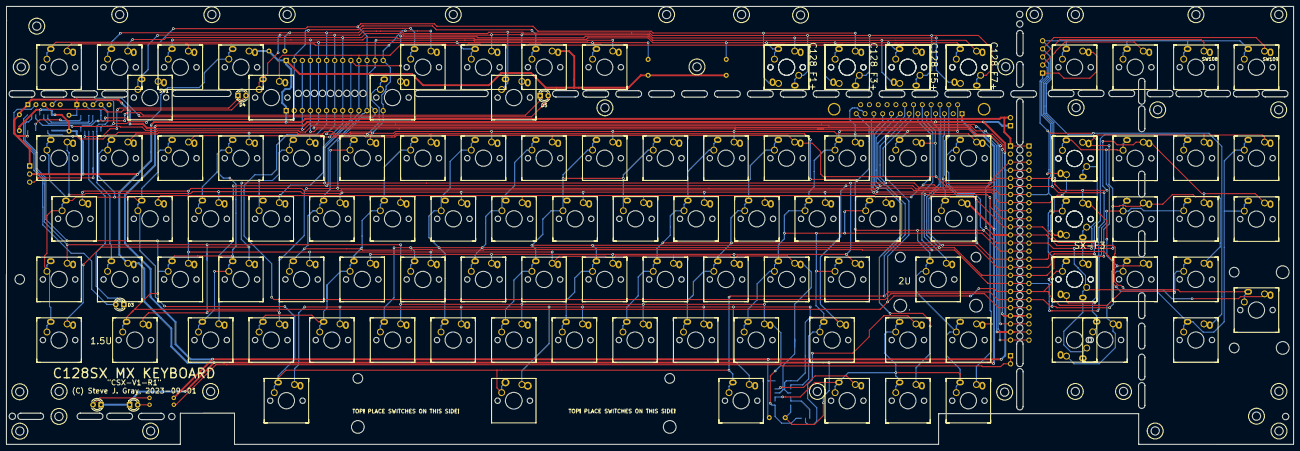
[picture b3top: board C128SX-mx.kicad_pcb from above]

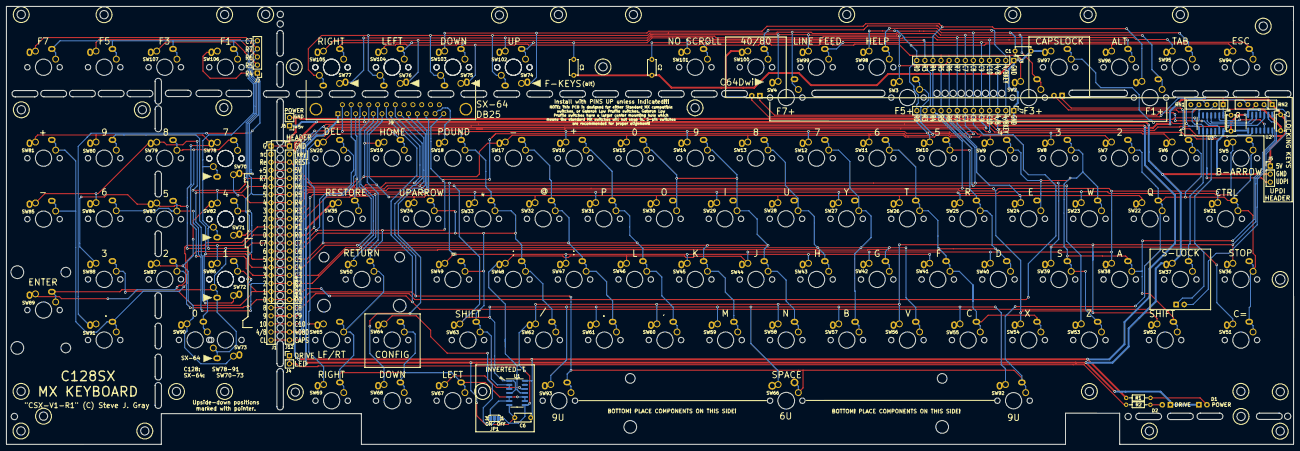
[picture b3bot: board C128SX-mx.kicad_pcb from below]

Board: 2 copper layers, 404.4 x 137.6 mm, 137 parts (23 on the bottom side), 43 nets.
